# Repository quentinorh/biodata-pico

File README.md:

# RPI PICO SYLVESTRE ORCHESTRE

Musique générée à partir des microvariations électriques d’une plante.

L’électronique du capteur est basée sur le [MIDI Sprout](https://github.com/electricityforprogress/MIDIsprout) de Sam Cusumano. Elle mesure la conductivité à la surface d’une feuille et produit un train d’impulsions. Un Raspberry Pi Pico 2 W compte la période de chaque impulsion, ouvre un point d’accès Wi-Fi et sert une interface web. Le navigateur du téléphone dessine le signal et le transforme en son avec des instruments [Faust](https://faust.grame.fr) issus d’[Ambient Garden](https://ambient.garden).

Réalisé par [Quentin Orhant](https://quentino.io) pour l’association [CC Lab](https://climatechangelab.org).

## Fonctionnement

```
feuille → capteur (impulsions) → Pico (périodes en µs) → Wi-Fi → navigateur (graphe + synthèse)
```

Le capteur oscille autour de 50 Hz, soit une période d’environ 20 000 µs. Plus la conductivité de la feuille change, plus cette période dérive. Le Pico ne fait pas de son : il mesure, filtre les valeurs aberrantes, et envoie les périodes au téléphone.

### Mesure sur le Pico

Une machine d’état PIO (`pulse_period` dans `pico_firmware/main.py`) compte la durée d’un cycle complet du signal, front montant à front montant. Elle tourne à 3 MHz et consomme trois cycles par pas, ce qui donne une résolution de 1 µs.

Chaque mesure est convertie en microsecondes. Les périodes hors de la fenêtre 100 µs – 250 000 µs sont écartées : ce sont des parasites de commutation, pas le signal de la plante. La LED du Pico clignote d’autant plus vite que les impulsions arrivent.

### Réseau et interface

Au démarrage, le Pico ouvre le point d’accès **Plante-Musicale** (réseau ouvert, voir `pico_firmware/config.py`) et sert l’interface sur `http://192.168.4.1`. Un petit serveur DNS répond à toute requête par l’adresse du Pico, ce qui déclenche le portail captif d’Android, d’iOS et de Windows.

L’interface est une page statique (`app/`) plus quelques routes :

| Route             | Rôle                                                               |
| ----------------- | ------------------------------------------------------------------- |
| `/api/stream`   | Flux Server-Sent Events des périodes (`intervals_us`, en µs)    |
| `/api/data`     | Même contenu, en une seule réponse JSON                           |
| `/api/status`   | SSID, adresse, broche du capteur, dernière période, RAM libre     |
| `/api/settings` | Bibliothèque de jeux de réglages, stockée dans `settings.json` |

Les fichiers de l’interface sont déposés en gzip sur le Pico et servis avec `Content-Encoding: gzip`. La bibliothèque de réglages reste à la racine du système de fichiers, en dehors du dossier `app`, pour survivre à un redéploiement.

### Du signal au son

Le navigateur ouvre le flux SSE, trace chaque période sur le graphe, et maintient deux seuils (haut et bas) que l’on peut déplacer à la main. Trois pistes lisent le même signal, chacune avec son instrument :

- **Ambiance** — suit toute la hauteur du graphe et l’agitation globale du signal. Elle module en continu un paramètre de l’instrument (fréquence, densité, filtre…).
- **Végétal** — ne réagit qu’entre les deux seuils. Les petites variations y sont très sensibles. Les extrema locaux déclenchent des notes, à un rythme borné par le BPM.
- **Toucher** — ce qui dépasse les seuils, en particulier les attaques. Une transition (par défaut 1,2 s) fait apparaître cette piste par-dessus le végétal, qui continue de jouer. Sans impulsions, tous les sons s’éteignent de la même façon.

Les instruments sont des patches Faust précompilés (WASM), joués par le moteur [Teasynth](https://github.com/pac-dev/Teasynth). Sur le Pico, servi en HTTP, le mixage passe par un `ScriptProcessor`. En HTTPS ou sur `localhost`, un `AudioWorklet` est utilisé à la place.

Les jeux de réglages (instruments, volumes, seuils, BPM) peuvent être enregistrés sur le Pico (jusqu’à 24), ou exportés et importés en JSON.

## Matériel

- Raspberry Pi Pico **2 W**, firmware MicroPython `RPI_PICO2_W`. Le Pico W d’origine n’a pas assez de flash pour l’interface et les 18 patches.
- Carte capteur V1 : oscillateur **LMC555** en 3,3 V, inspiré du MIDI Sprout. Schéma, synthèse et nomenclature dans `pcb/` (`synthese-pcb-v1.md`, `BOM-v1-mouser.csv`).
- Sortie du 555 sur **GP15**, broche physique 20. Le pull-down est celui du Pico (firmware), pas une résistance sur la carte.
- Un téléphone ou un ordinateur pour le son : la synthèse tourne dans le navigateur, pas sur le Pico.

## Utilisation

1. Assembler le PCB et le Raspberry pi Pico, les électrodes sur la feuille, puis alimenter le Pico.
2. Rejoindre le Wi-Fi **Plante-Musicale**.
3. Ouvrir `http://192.168.4.1` (le portail captif y mène souvent tout seul).
4. Autoriser le son, puis régler les trois pistes depuis le panneau.

Pour remettre un mot de passe WPA2, passer `WIFI_OPEN` à `False` dans `pico_firmware/config.py`. Le mot de passe prévu est `biosonique` (8 caractères minimum).

## Développer sans le Pico

`tools/dev_server.py` sert le dossier `app` et simule l’API du Pico avec un signal synthétique à 50 Hz (dérive lente et « touchers »).

```bash
python tools/dev_server.py
```

L’interface est alors sur `http://localhost:8080`.

## Déployer sur le Pico

L’interpréteur MicroPython s’installe une fois, à la main. `tools/deploy.py` copie ensuite le programme et l’interface ; il ne remplace pas cet interpréteur.

1. Télécharger le firmware du **Pico 2 W**, variante `RPI_PICO2_W` : [RPI_PICO2_W-latest.uf2](https://micropython.org/download/RPI_PICO2_W/RPI_PICO2_W-latest.uf2) ([autres versions](https://micropython.org/download/RPI_PICO2_W/)). C’est la build pour la puce RP2350 et le Wi-Fi de cette carte.
2. Maintenir le bouton **BOOTSEL** en branchant le câble USB. Un disque nommé **RP2350** apparaît.
3. Copier le `.uf2` sur ce disque. La carte redémarre sous MicroPython et le disque disparaît.

Pour changer de version plus tard, la même séquence suffit. Si MicroPython tourne déjà, `machine.bootloader()` au REPL ouvre aussi ce disque.

Le Pico doit ensuite être branché en USB, avec `mpremote` installé (`pip install mpremote`). Le script compresse l’interface, copie `main.py` et `config.py`, puis redémarre la carte. Les sources `.dsp` restent sur le PC : seuls les WASM et le catalogue partent sur la flash.

```bash
python tools/deploy.py
python tools/deploy.py --port COM16
python tools/deploy.py --quick    # firmware et fichiers principaux seulement
```

Si LittleFS est plein, le script reformate le système de fichiers. Il relit `settings.json` avant, et le réécrit après.

## Arborescence

```
pico_firmware/     MicroPython : mesure PIO, point d'accès, HTTP, DNS captif
app/               Interface web, graphe, sonification, patches Faust
pcb/               Carte capteur V1 : schéma KiCad, synthèse, nomenclature
tools/deploy.py    Copie firmware + interface gzippée sur le Pico 2 W
tools/dev_server.py  Simulateur de l'API, sans matériel
```

## Dépendances

- [MIDI Sprout](https://github.com/electricityforprogress/MIDIsprout) — électronique du capteur, Sam Cusumano
- [Ambient Garden](https://ambient.garden) — instruments Faust du paysage sonore
- [Teasynth](https://github.com/pac-dev/Teasynth) — lecture de ces patches dans le navigateur
- [Faust](https://faust.grame.fr) — langage de synthèse, GRAME
- [MicroPython](https://micropython.org) — firmware du Pico 2 W

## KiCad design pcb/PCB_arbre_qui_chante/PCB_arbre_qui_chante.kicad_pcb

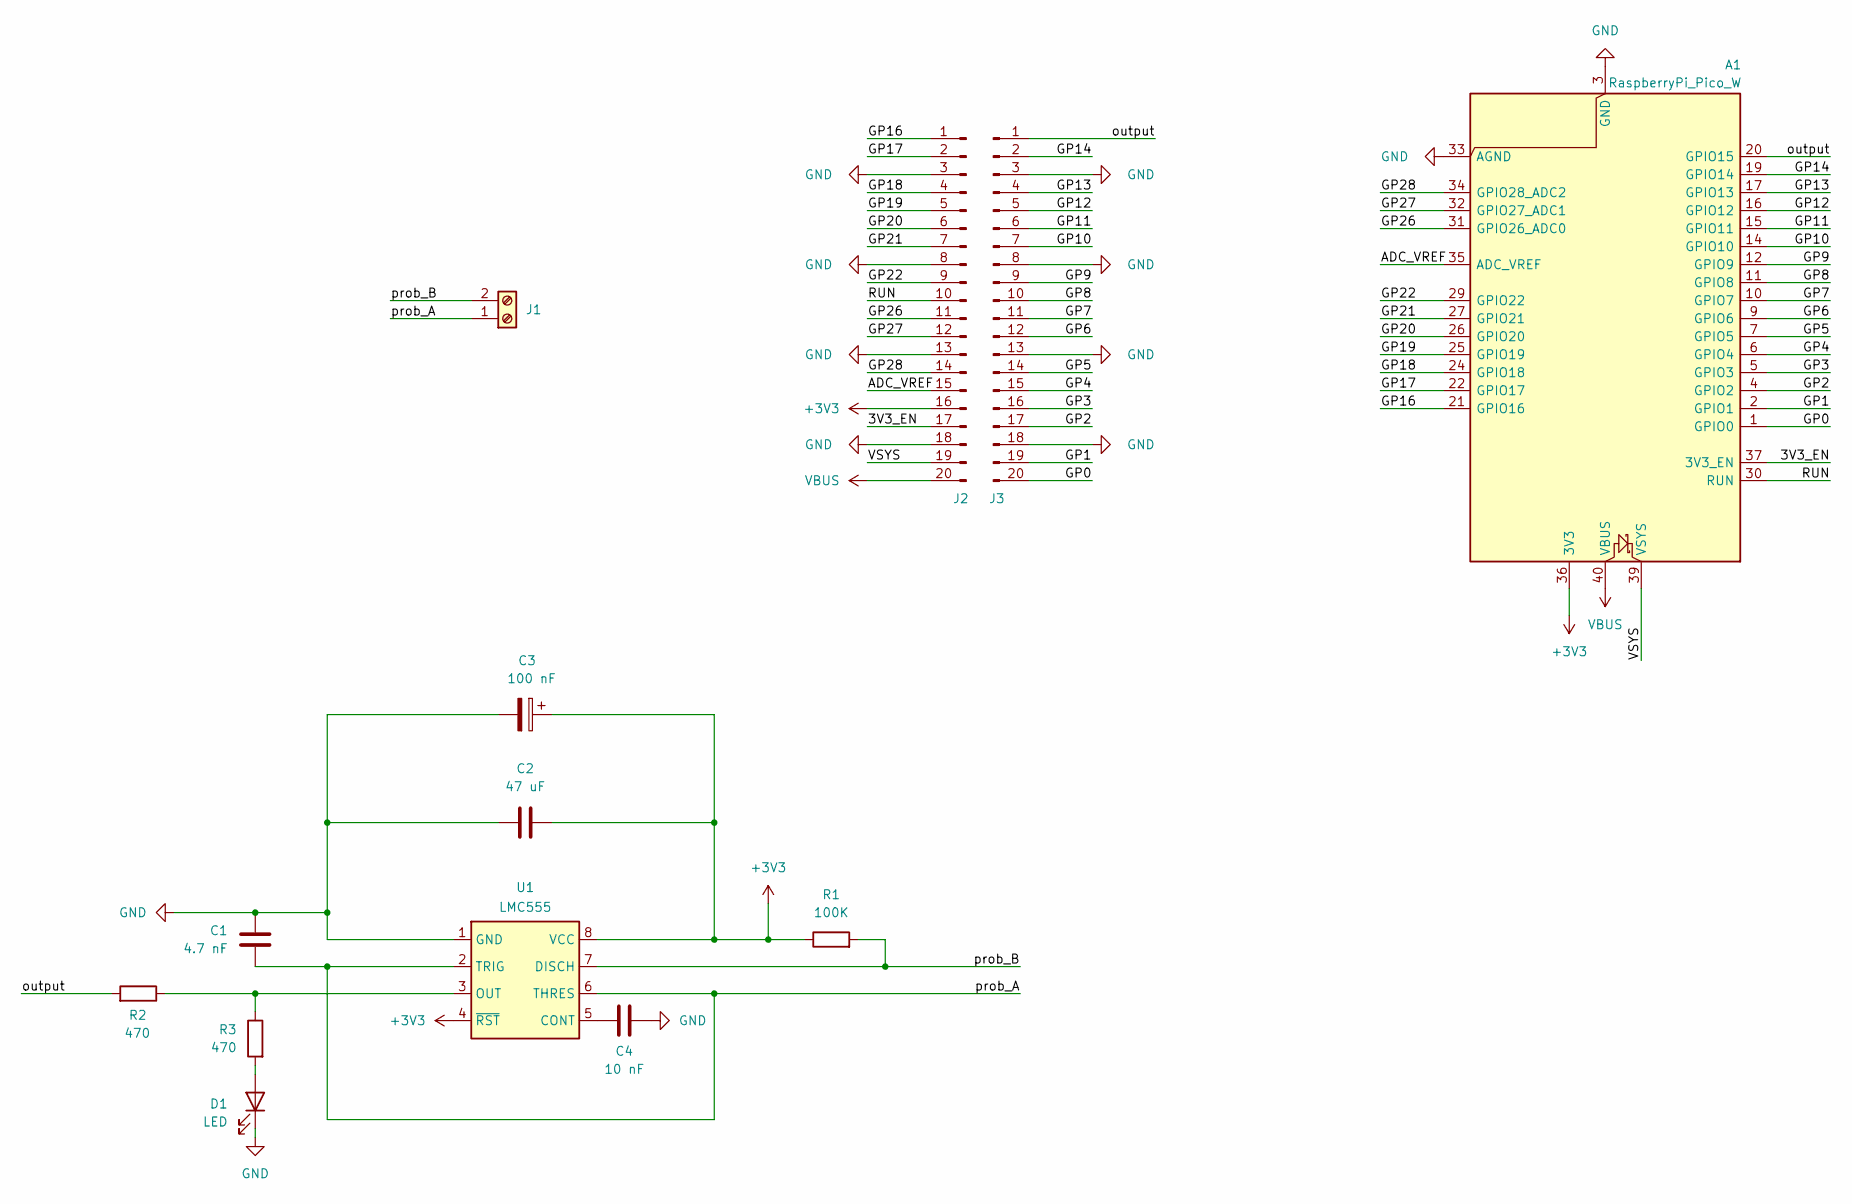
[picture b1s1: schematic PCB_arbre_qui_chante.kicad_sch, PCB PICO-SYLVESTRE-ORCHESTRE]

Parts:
A1: RaspberryPi_Pico_W; RaspberryPi_Pico_Common_THT-pinsocket
C1: 4.7 nF
C2: 47 uF
C3: 100 nF
C4: 10 nF
D1: LED
J1: Screw_Terminal_01x02
J2, J3: Conn_01x20_Pin
R1: 100K
R2, R3: 470
U1: LMC555; DIP-8_W7.62mm

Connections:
+3V3: A1.36 (3V3), C2.1, C3.1, J2.16, R1.1, U1.4 (~RST), U1.8 (VCC)
/3V3_EN: A1.37 (3V3_EN), J2.17
/ADC_VREF: A1.35 (ADC_VREF), J2.15
/GP0: A1.1 (GPIO0), J3.20
/GP1: A1.2 (GPIO1), J3.19
/GP2: A1.4 (GPIO2), J3.17
/GP3: A1.5 (GPIO3), J3.16
/GP4: A1.6 (GPIO4), J3.15
/GP5: A1.7 (GPIO5), J3.14
/GP6: A1.9 (GPIO6), J3.12
/GP7: A1.10 (GPIO7), J3.11
/GP8: A1.11 (GPIO8), J3.10
/GP9: A1.12 (GPIO9), J3.9
/GP10: A1.14 (GPIO10), J3.7
/GP11: A1.15 (GPIO11), J3.6
/GP12: A1.16 (GPIO12), J3.5
/GP13: A1.17 (GPIO13), J3.4
/GP14: A1.19 (GPIO14), J3.2
/GP16: A1.21 (GPIO16), J2.1
/GP17: A1.22 (GPIO17), J2.2
/GP18: A1.24 (GPIO18), J2.4
/GP19: A1.25 (GPIO19), J2.5
/GP20: A1.26 (GPIO20), J2.6
/GP21: A1.27 (GPIO21), J2.7
/GP22: A1.29 (GPIO22), J2.9
/GP26: A1.31 (GPIO26_ADC0), J2.11
/GP27: A1.32 (GPIO27_ADC1), J2.12
/GP28: A1.34 (GPIO28_ADC2), J2.14
/RUN: A1.30 (RUN), J2.10
/VSYS: A1.39 (VSYS), J2.19
/output: A1.20 (GPIO15), J3.1, R2.2
/prob_A: C1.2, J1.1, U1.2 (TRIG), U1.6 (THRES)
/prob_B: J1.2, R1.2, U1.7 (DISCH)
GND: A1.3 (GND), A1.8 (GND), A1.13 (GND), A1.18 (GND), A1.23 (GND), A1.28 (GND), A1.33 (AGND), A1.38 (GND), C1.1, C2.2, C3.2, C4.1, D1.1 (K), J2.3, J2.8, J2.13, J2.18, J3.3, J3.8, J3.13, J3.18, U1.1 (GND)
unnamed: D1.2 (A), R3.2
unnamed: C4.2, U1.5 (CONT)
unnamed: R2.1, R3.1, U1.3 (OUT)
VBUS: A1.40 (VBUS), J2.20

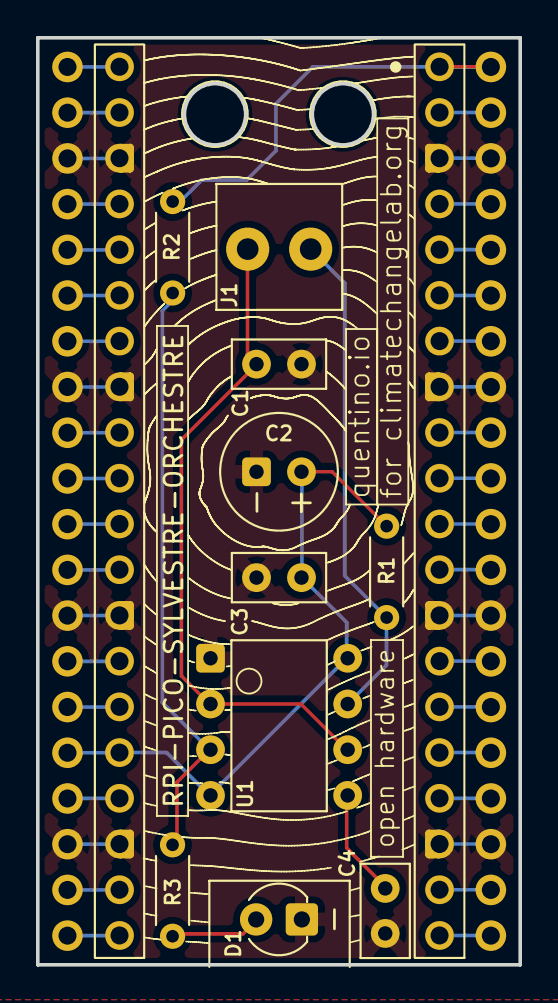
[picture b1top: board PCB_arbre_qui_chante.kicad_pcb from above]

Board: 2 copper layers, 26.8 x 51.5 mm, 13 parts (0 on the bottom side), 38 nets.
